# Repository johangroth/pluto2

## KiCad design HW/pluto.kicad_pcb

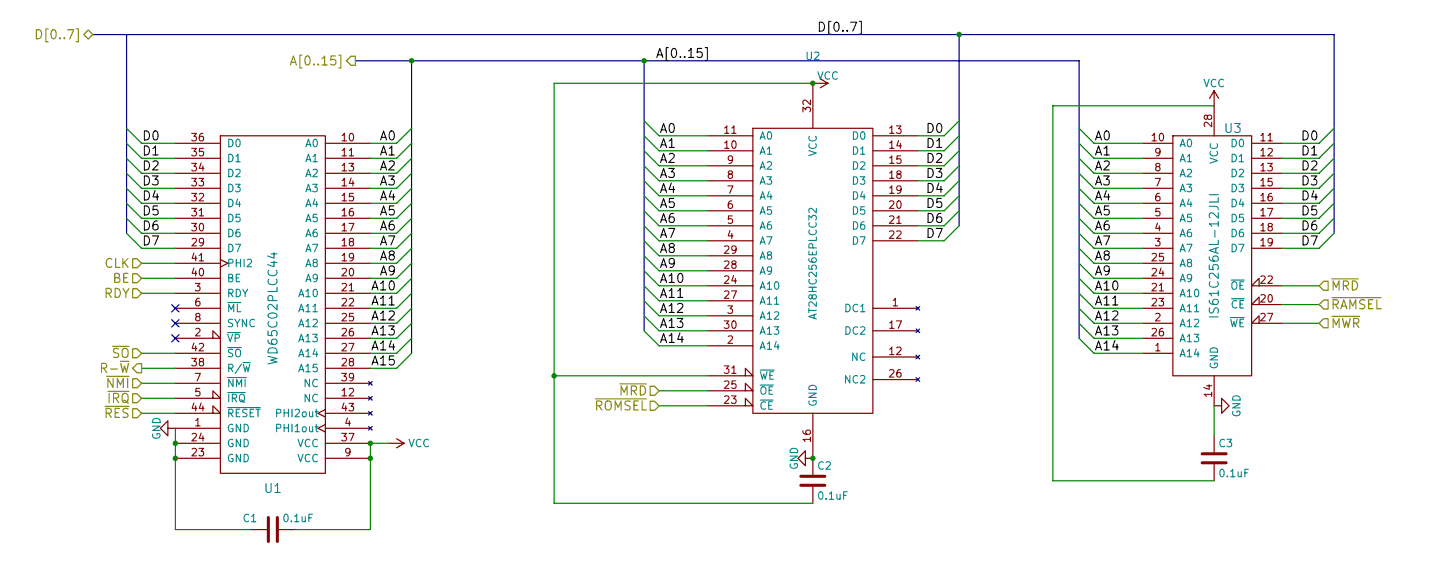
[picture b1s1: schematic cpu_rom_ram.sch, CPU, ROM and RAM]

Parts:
C1, C2, C3: 0.1uF; C_0805_2012Metric_Pad1.15x1.40mm_HandSolder
U1: WD65C02PLCC44; PLCC-44_THT-Socket
U2: AT28HC256EPLCC32; PLCC-32_THT-Socket
U3: IS61C256AL-12JLI; SOJ-28_7.585x18.12mm_P1.27mm

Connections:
/16bit IDE interface/A0: U1.10 (A0), U2.11 (A0), U3.10 (A0); also elsewhere on the board
/16bit IDE interface/A1: U1.11 (A1), U2.10 (A1), U3.9 (A1); also elsewhere on the board
/16bit IDE interface/A2: U1.13 (A2), U2.9 (A2), U3.8 (A2); also elsewhere on the board
/16bit IDE interface/A3: U1.14 (A3), U2.8 (A3), U3.7 (A3); also elsewhere on the board
/16bit IDE interface/CLK: U1.41 (PHI2); also elsewhere on the board
/16bit IDE interface/D0: U1.36 (D0), U2.13 (D0), U3.11 (D0); also elsewhere on the board
/16bit IDE interface/D1: U1.35 (D1), U2.14 (D1), U3.12 (D1); also elsewhere on the board
/16bit IDE interface/D2: U1.34 (D2), U2.15 (D2), U3.13 (D2); also elsewhere on the board
/16bit IDE interface/D3: U1.33 (D3), U2.18 (D3), U3.15 (D3); also elsewhere on the board
/16bit IDE interface/D4: U1.32 (D4), U2.19 (D4), U3.16 (D4); also elsewhere on the board
/16bit IDE interface/D5: U1.31 (D5), U2.20 (D5), U3.17 (D5); also elsewhere on the board
/16bit IDE interface/D6: U1.30 (D6), U2.21 (D6), U3.18 (D6); also elsewhere on the board
/16bit IDE interface/D7: U1.29 (D7), U2.22 (D7), U3.19 (D7); also elsewhere on the board
/16bit IDE interface/R-~W: U1.38 (R/~W); also elsewhere on the board
/16bit IDE interface/~IRQ: U1.5 (~IRQ); also elsewhere on the board
/16bit IDE interface/~RES: U1.44 (~RESET); also elsewhere on the board
/Address decoding and support section/A5: U1.16 (A5), U2.6 (A5), U3.5 (A5); also elsewhere on the board
/Address decoding and support section/A6: U1.17 (A6), U2.5 (A6), U3.4 (A6); also elsewhere on the board
/Address decoding and support section/A7: U1.18 (A7), U2.4 (A7), U3.3 (A7); also elsewhere on the board
/Address decoding and support section/A8: U1.19 (A8), U2.29 (A8), U3.25 (A8); also elsewhere on the board
/Address decoding and support section/A9: U1.20 (A9), U2.28 (A9), U3.24 (A9); also elsewhere on the board
/Address decoding and support section/A10: U1.21 (A10), U2.24 (A10), U3.21 (A10); also elsewhere on the board
/Address decoding and support section/A11: U1.22 (A11), U2.27 (A11), U3.23 (A11); also elsewhere on the board
/Address decoding and support section/A12: U1.25 (A12), U2.3 (A12), U3.2 (A12); also elsewhere on the board
/Address decoding and support section/A13: U1.26 (A13), U2.30 (A13), U3.26 (A13); also elsewhere on the board
/Address decoding and support section/A14: U1.27 (A14), U2.2 (A14), U3.1 (A14); also elsewhere on the board
/Address decoding and support section/A15: U1.28 (A15); also elsewhere on the board
/Address decoding and support section/BE: U1.40 (BE); also elsewhere on the board
/Address decoding and support section/RDY: U1.3 (RDY); also elsewhere on the board
/Address decoding and support section/~MRD: U2.25 (~OE), U3.22 (~OE); also elsewhere on the board
/Address decoding and support section/~MWR: U3.27 (~WE); also elsewhere on the board
/Address decoding and support section/~NMI: U1.7 (~NMI); also elsewhere on the board
/Address decoding and support section/~RAMSEL: U3.20 (~CE); also elsewhere on the board
/Address decoding and support section/~ROMSEL: U2.23 (~CE); also elsewhere on the board
/Address decoding and support section/~SO: U1.42 (~SO); also elsewhere on the board
/CPU, ROM and RAM/A4: U1.15 (A4), U2.7 (A4), U3.6 (A4); also elsewhere on the board
GND: C1.1, C2.1, C3.1, U1.1 (GND), U1.23 (GND), U1.24 (GND), U2.16 (GND), U3.14 (GND); also elsewhere on the board
VCC: C1.2, C2.2, C3.2, U1.9 (VCC), U1.37 (VCC), U2.31 (~WE), U2.32 (VCC), U3.28 (VCC); also elsewhere on the board

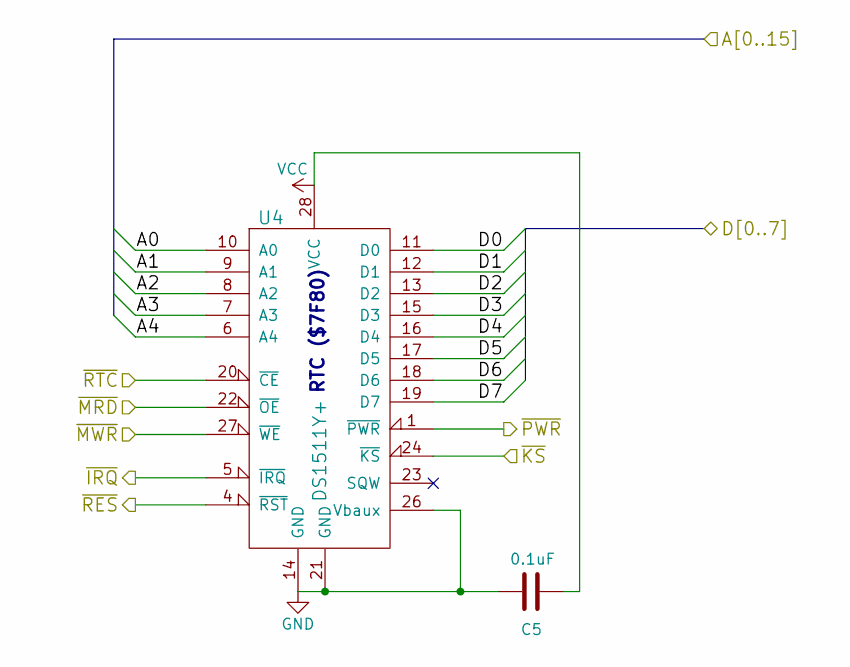
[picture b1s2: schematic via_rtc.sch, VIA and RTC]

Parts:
C5: 0.1uF; C_0805_2012Metric_Pad1.15x1.40mm_HandSolder
U4: DS1511Y+; DIP-28_W15.24mm_Socket

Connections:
/16bit IDE interface/A0: U4.10 (A0); also elsewhere on the board
/16bit IDE interface/A1: U4.9 (A1); also elsewhere on the board
/16bit IDE interface/A2: U4.8 (A2); also elsewhere on the board
/16bit IDE interface/A3: U4.7 (A3); also elsewhere on the board
/16bit IDE interface/D0: U4.11 (D0); also elsewhere on the board
/16bit IDE interface/D1: U4.12 (D1); also elsewhere on the board
/16bit IDE interface/D2: U4.13 (D2); also elsewhere on the board
/16bit IDE interface/D3: U4.15 (D3); also elsewhere on the board
/16bit IDE interface/D4: U4.16 (D4); also elsewhere on the board
/16bit IDE interface/D5: U4.17 (D5); also elsewhere on the board
/16bit IDE interface/D6: U4.18 (D6); also elsewhere on the board
/16bit IDE interface/D7: U4.19 (D7); also elsewhere on the board
/16bit IDE interface/~IRQ: U4.5 (~IRQ); also elsewhere on the board
/16bit IDE interface/~RES: U4.4 (~RST); also elsewhere on the board
/Address decoding and support section/~KS: U4.24 (~KS); also elsewhere on the board
/Address decoding and support section/~MRD: U4.22 (~OE); also elsewhere on the board
/Address decoding and support section/~MWR: U4.27 (~WE); also elsewhere on the board
/Address decoding and support section/~PWR: U4.1 (~PWR); also elsewhere on the board
/Address decoding and support section/~RTC: U4.20 (~CE); also elsewhere on the board
/CPU, ROM and RAM/A4: U4.6 (A4); also elsewhere on the board
GND: C5.2, U4.14 (GND), U4.21 (GND), U4.26 (Vbaux); also elsewhere on the board
VCC: C5.1, U4.28 (VCC); also elsewhere on the board

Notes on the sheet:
RTC ($7F80)

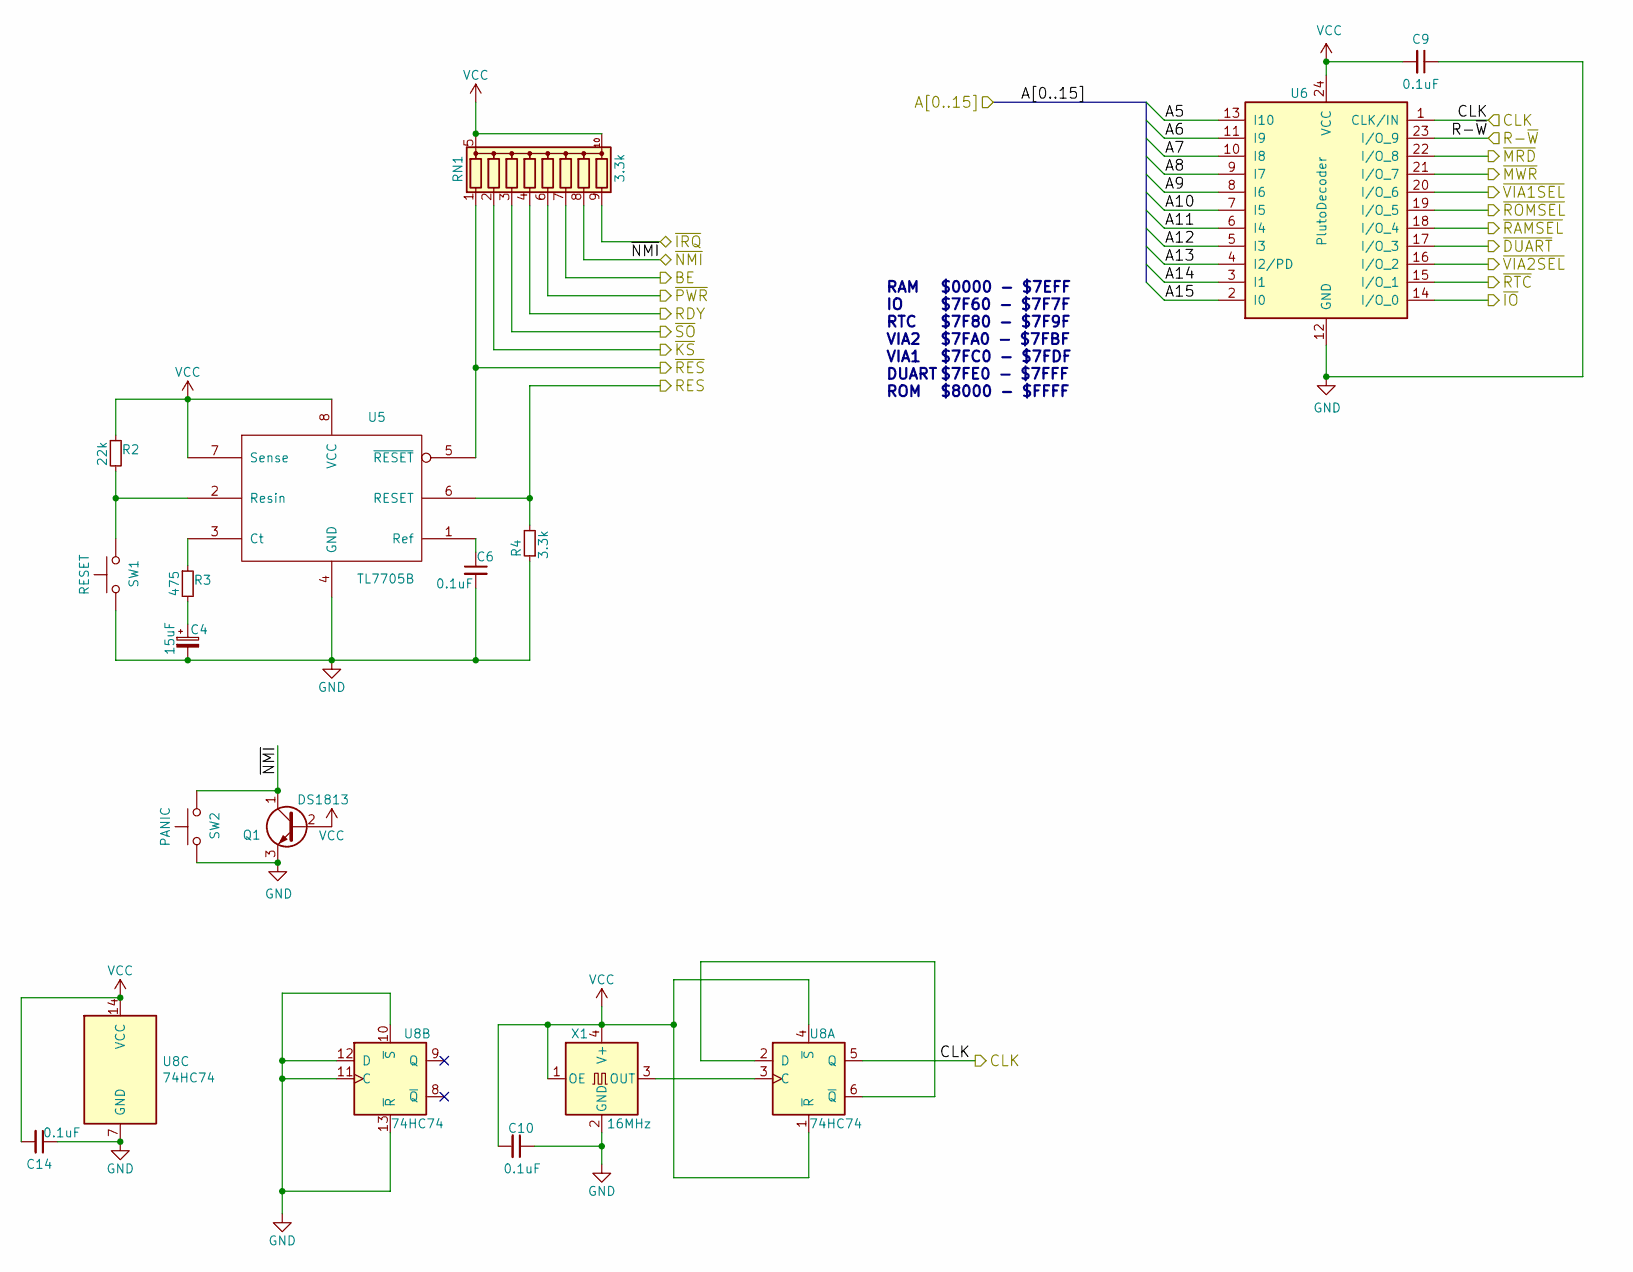
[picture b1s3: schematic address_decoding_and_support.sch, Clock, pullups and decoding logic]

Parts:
C4: 15uF; CP_EIA-3528-15_AVX-H_Pad1.50x2.35mm_HandSolder
C6, C9, C10, C14: 0.1uF; C_0805_2012Metric_Pad1.15x1.40mm_HandSolder
Q1: DS1813; SOT-23_Handsoldering
R2: 22k; R_1206_3216Metric_Pad1.42x1.75mm_HandSolder
R3: 475; R_1206_3216Metric_Pad1.42x1.75mm_HandSolder
R4: 3.3k; R_1206_3216Metric_Pad1.42x1.75mm_HandSolder
RN1: 3.3k; R_Array_Convex_5x1206
SW1: RESET; SW_PUSH_6mm_H4.3mm
SW2: PANIC; SW_PUSH_6mm_H4.3mm
U5: TL7705B; SOIC-8_3.9x4.9mm_P1.27mm
U6: PlutoDecoder; DIP-24_W7.62mm_Socket
U8: 74HC74; SOIC-14_3.9x8.7mm_P1.27mm
X1: 16MHz; Oscillator_SMD_SeikoEpson_SG8002CA-4Pin_7.0x5.0mm

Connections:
/16bit IDE interface/CLK: U6.1 (CLK/IN), U8.5 (Q); also elsewhere on the board
/16bit IDE interface/R-~W: U6.23 (I/O_9); also elsewhere on the board
/16bit IDE interface/~IRQ: RN1.9 (R8); also elsewhere on the board
/16bit IDE interface/~RES: RN1.1 (R1), U5.5 (~RESET); also elsewhere on the board
/16bit IDE interface/~VIA1SEL: U6.20 (I/O_6); also elsewhere on the board
/16bit IDE interface/~VIA2SEL: U6.16 (I/O_2); also elsewhere on the board
/Address decoding and support section/A5: U6.13 (I10); also elsewhere on the board
/Address decoding and support section/A6: U6.11 (I9); also elsewhere on the board
/Address decoding and support section/A7: U6.10 (I8); also elsewhere on the board
/Address decoding and support section/A8: U6.9 (I7); also elsewhere on the board
/Address decoding and support section/A9: U6.8 (I6); also elsewhere on the board
/Address decoding and support section/A10: U6.7 (I5); also elsewhere on the board
/Address decoding and support section/A11: U6.6 (I4); also elsewhere on the board
/Address decoding and support section/A12: U6.5 (I3); also elsewhere on the board
/Address decoding and support section/A13: U6.4 (I2/PD); also elsewhere on the board
/Address decoding and support section/A14: U6.3 (I1); also elsewhere on the board
/Address decoding and support section/A15: U6.2 (I0); also elsewhere on the board
/Address decoding and support section/BE: RN1.7 (R6); also elsewhere on the board
/Address decoding and support section/RDY: RN1.4 (R4); also elsewhere on the board
/Address decoding and support section/RES: R4.2, U5.6 (RESET); also elsewhere on the board
/Address decoding and support section/~DUART: U6.17 (I/O_3); also elsewhere on the board
/Address decoding and support section/~IO: U6.14 (I/O_0); also elsewhere on the board
/Address decoding and support section/~KS: RN1.2 (R2); also elsewhere on the board
/Address decoding and support section/~MRD: U6.22 (I/O_8); also elsewhere on the board
/Address decoding and support section/~MWR: U6.21 (I/O_7); also elsewhere on the board
/Address decoding and support section/~NMI: Q1.1 (C), RN1.8 (R7), SW2.2; also elsewhere on the board
/Address decoding and support section/~PWR: RN1.6 (R5); also elsewhere on the board
/Address decoding and support section/~RAMSEL: U6.18 (I/O_4); also elsewhere on the board
/Address decoding and support section/~ROMSEL: U6.19 (I/O_5); also elsewhere on the board
/Address decoding and support section/~RTC: U6.15 (I/O_1); also elsewhere on the board
/Address decoding and support section/~SO: RN1.3 (R3); also elsewhere on the board
GND: C4.2, C6.2, C9.1, C10.1, C14.1, Q1.3 (E), R4.1, SW1.1, SW2.1, U5.4 (GND), U6.12 (GND), U8.7 (GND), U8.10 (~S), U8.11 (C), U8.12 (D), U8.13 (~R), X1.2 (GND); also elsewhere on the board
unnamed: C4.1, R3.2
unnamed: C6.1, U5.1 (Ref)
unnamed: R2.2, SW1.2, U5.2 (Resin)
unnamed: R3.1, U5.3 (Ct)
unnamed: U8.2 (D), U8.6 (~Q)
unnamed: U8.3 (C), X1.3 (OUT)
VCC: C9.2, C10.2, C14.2, Q1.2 (B), R2.1, RN1.5 (common), RN1.10 (common), U5.7 (Sense), U5.8 (VCC), U6.24 (VCC), U8.1 (~R), U8.4 (~S), U8.14 (VCC), X1.1 (OE), X1.4 (V+); also elsewhere on the board

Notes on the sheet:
RAM IO RTC VIA2 VIA1 DUART ROM
$0000 - $7EFF $7F60 - $7F7F $7F80 - $7F9F $7FA0 - $7FBF $7FC0 - $7FDF $7FE0 - $7FFF $8000 - $FFFF

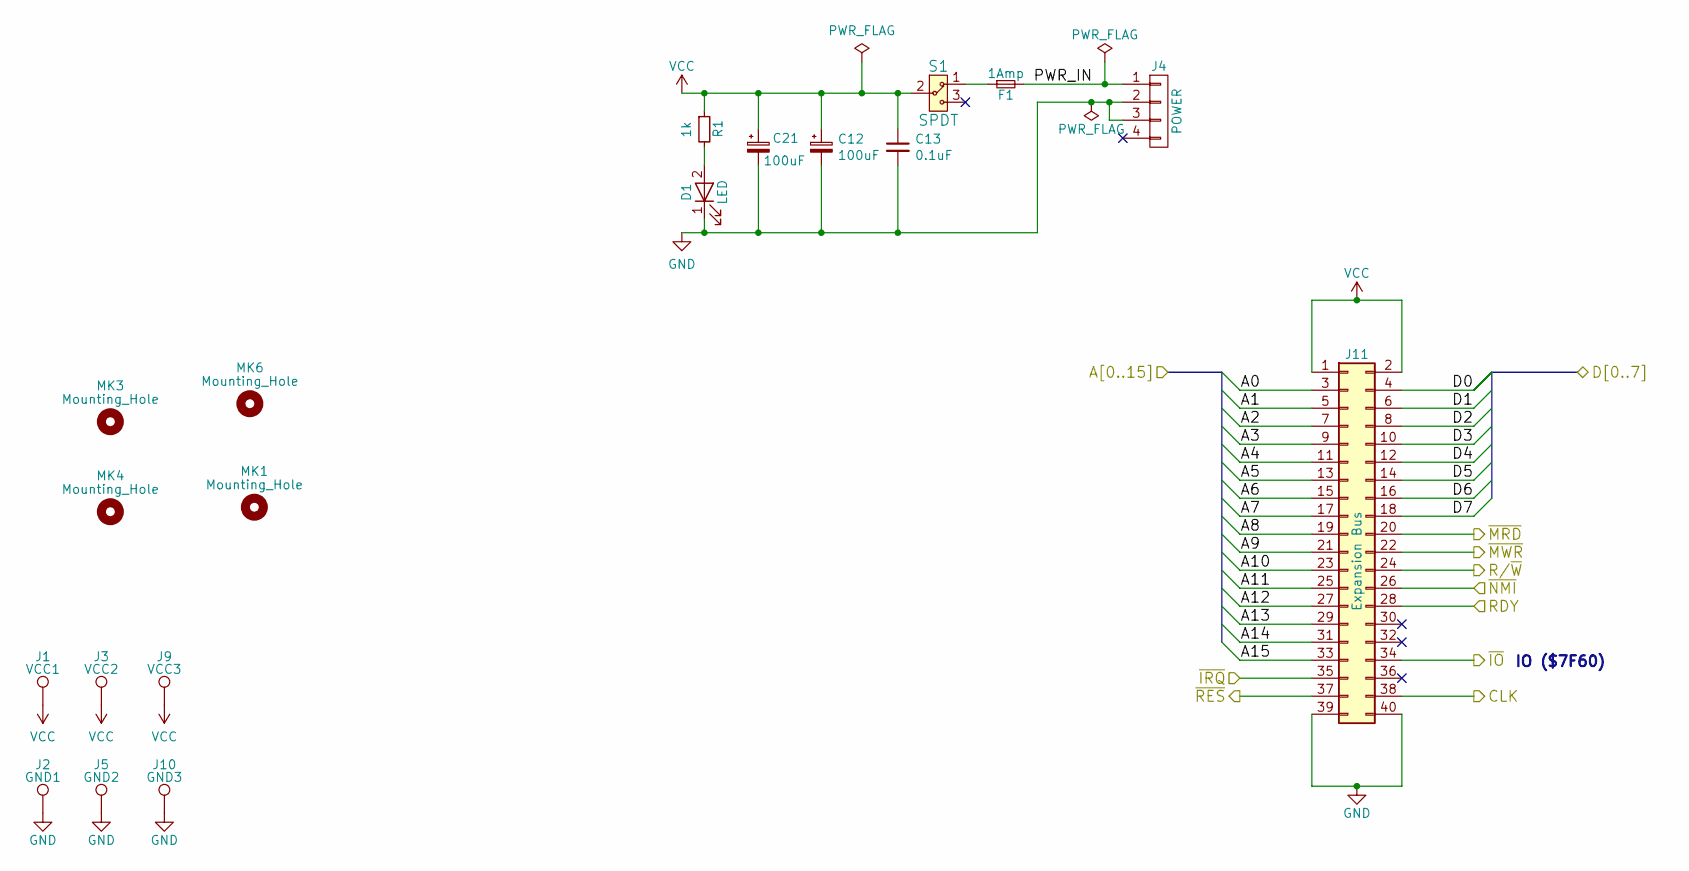
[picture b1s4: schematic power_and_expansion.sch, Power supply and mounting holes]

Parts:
C12, C21: 100uF; CP_EIA-3528-15_AVX-H_Pad1.50x2.35mm_HandSolder
C13: 0.1uF; C_0805_2012Metric_Pad1.15x1.40mm_HandSolder
D1: LED; LED_D3.0mm
F1: 1Amp; FUSE_0154004.DR
J1: VCC1; PinHeader_1x01_P2.54mm_Vertical
J2: GND1; PinHeader_1x01_P2.54mm_Vertical
J3: VCC2; PinHeader_1x01_P2.54mm_Vertical
J4: POWER; Molex_Nano-Fit_105313-xx04_1x04_P2.50mm_Horizontal
J5: GND2; PinHeader_1x01_P2.54mm_Vertical
J9: VCC3; PinHeader_1x01_P2.54mm_Vertical
J10: GND3; PinHeader_1x01_P2.54mm_Vertical
J11: Expansion Bus; IDC-Header_2x20_P2.54mm_Vertical
MK1, MK3, MK4, MK6: Mounting_Hole; MountingHole_3.2mm_M3_Pad
R1: 1k; R_1206_3216Metric_Pad1.42x1.75mm_HandSolder
S1: SPDT; SW-SPDT-0900766b81587629

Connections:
/16bit IDE interface/A0: J11.3; also elsewhere on the board
/16bit IDE interface/A1: J11.5; also elsewhere on the board
/16bit IDE interface/A2: J11.7; also elsewhere on the board
/16bit IDE interface/A3: J11.9; also elsewhere on the board
/16bit IDE interface/CLK: J11.38; also elsewhere on the board
/16bit IDE interface/D0: J11.4; also elsewhere on the board
/16bit IDE interface/D1: J11.6; also elsewhere on the board
/16bit IDE interface/D2: J11.8; also elsewhere on the board
/16bit IDE interface/D3: J11.10; also elsewhere on the board
/16bit IDE interface/D4: J11.12; also elsewhere on the board
/16bit IDE interface/D5: J11.14; also elsewhere on the board
/16bit IDE interface/D6: J11.16; also elsewhere on the board
/16bit IDE interface/D7: J11.18; also elsewhere on the board
/16bit IDE interface/R-~W: J11.24; also elsewhere on the board
/16bit IDE interface/~IRQ: J11.35; also elsewhere on the board
/16bit IDE interface/~RES: J11.37; also elsewhere on the board
/Address decoding and support section/A5: J11.13; also elsewhere on the board
/Address decoding and support section/A6: J11.15; also elsewhere on the board
/Address decoding and support section/A7: J11.17; also elsewhere on the board
/Address decoding and support section/A8: J11.19; also elsewhere on the board
/Address decoding and support section/A9: J11.21; also elsewhere on the board
/Address decoding and support section/A10: J11.23; also elsewhere on the board
/Address decoding and support section/A11: J11.25; also elsewhere on the board
/Address decoding and support section/A12: J11.27; also elsewhere on the board
/Address decoding and support section/A13: J11.29; also elsewhere on the board
/Address decoding and support section/A14: J11.31; also elsewhere on the board
/Address decoding and support section/A15: J11.33; also elsewhere on the board
/Address decoding and support section/RDY: J11.28; also elsewhere on the board
/Address decoding and support section/~IO: J11.34; also elsewhere on the board
/Address decoding and support section/~MRD: J11.20; also elsewhere on the board
/Address decoding and support section/~MWR: J11.22; also elsewhere on the board
/Address decoding and support section/~NMI: J11.26; also elsewhere on the board
/CPU, ROM and RAM/A4: J11.11; also elsewhere on the board
/Power and mounting holes/PWR_IN: F1.2, J4.1
GND: C12.2, C13.2, C21.2, D1.1 (K), J2.1, J4.2, J4.3, J5.1, J10.1, J11.39, J11.40; also elsewhere on the board
unnamed: D1.2 (A), R1.2
unnamed: F1.1, S1.1
VCC: C12.1, C13.1, C21.1, J1.1, J3.1, J9.1, J11.1, J11.2, R1.1, S1.2 (COM); also elsewhere on the board

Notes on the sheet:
IO ($7F60)

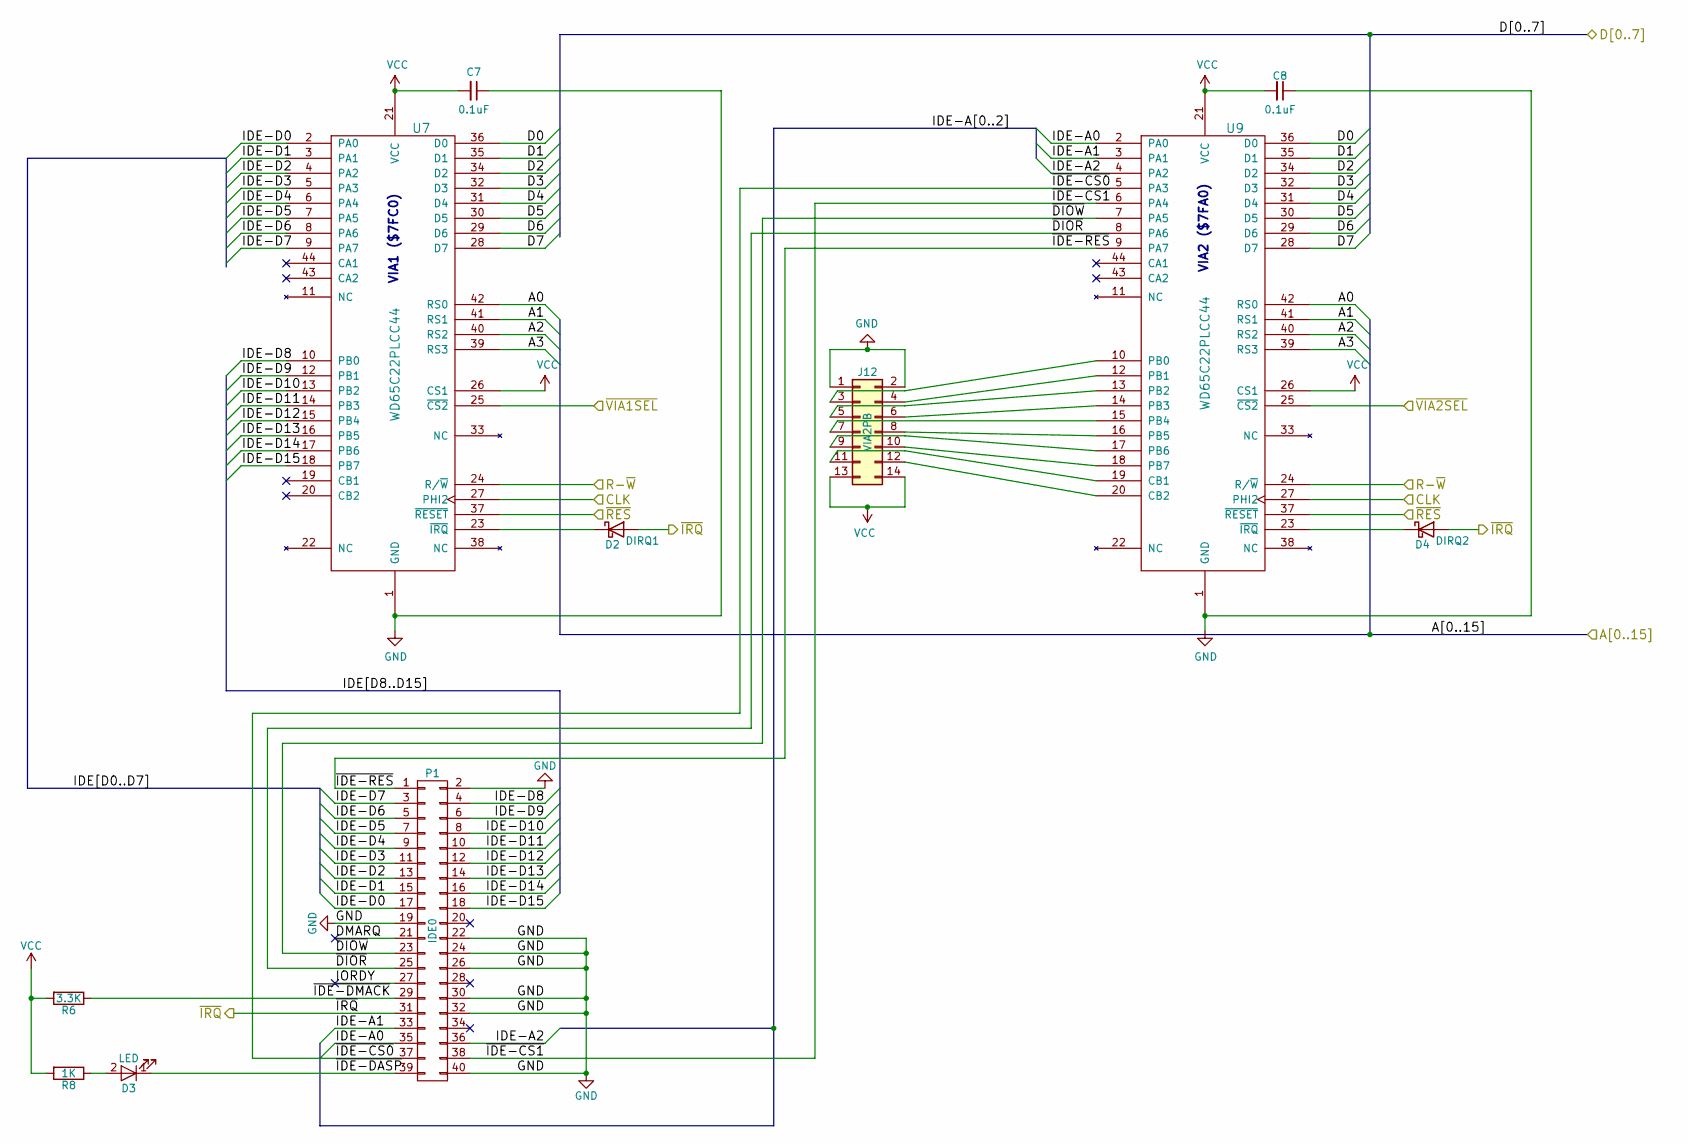
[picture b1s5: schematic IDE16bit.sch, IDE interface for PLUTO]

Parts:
C7, C8: 0.1uF; C_0805_2012Metric_Pad1.15x1.40mm_HandSolder
D2: DIRQ1; D_SOD-323_HandSoldering
D3: LED; LED_D3.0mm
D4: DIRQ2; D_SOD-323_HandSoldering
J12: VIA2PB; IDC-Header_2x07_P2.54mm_Vertical
P1: IDE0; IDC-Header_2x20_P2.54mm_Vertical
R6: 3.3K; R_1206_3216Metric_Pad1.42x1.75mm_HandSolder
R8: 1K; R_1206_3216Metric_Pad1.42x1.75mm_HandSolder
U7, U9: WD65C22PLCC44; PLCC-44_THT-Socket

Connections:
/16bit IDE interface/A0: U7.42 (RS0), U9.42 (RS0); also elsewhere on the board
/16bit IDE interface/A1: U7.41 (RS1), U9.41 (RS1); also elsewhere on the board
/16bit IDE interface/A2: U7.40 (RS2), U9.40 (RS2); also elsewhere on the board
/16bit IDE interface/A3: U7.39 (RS3), U9.39 (RS3); also elsewhere on the board
/16bit IDE interface/CLK: U7.27 (PHI2), U9.27 (PHI2); also elsewhere on the board
/16bit IDE interface/D0: U7.36 (D0), U9.36 (D0); also elsewhere on the board
/16bit IDE interface/D1: U7.35 (D1), U9.35 (D1); also elsewhere on the board
/16bit IDE interface/D2: U7.34 (D2), U9.34 (D2); also elsewhere on the board
/16bit IDE interface/D3: U7.32 (D3), U9.32 (D3); also elsewhere on the board
/16bit IDE interface/D4: U7.31 (D4), U9.31 (D4); also elsewhere on the board
/16bit IDE interface/D5: U7.30 (D5), U9.30 (D5); also elsewhere on the board
/16bit IDE interface/D6: U7.29 (D6), U9.29 (D6); also elsewhere on the board
/16bit IDE interface/D7: U7.28 (D7), U9.28 (D7); also elsewhere on the board
/16bit IDE interface/DMARQ: P1.21
/16bit IDE interface/IDE-A0: P1.35, U9.2 (PA0)
/16bit IDE interface/IDE-A1: P1.33, U9.3 (PA1)
/16bit IDE interface/IDE-A2: P1.36, U9.4 (PA2)
/16bit IDE interface/IDE-D0: P1.17, U7.2 (PA0)
/16bit IDE interface/IDE-D1: P1.15, U7.3 (PA1)
/16bit IDE interface/IDE-D2: P1.13, U7.4 (PA2)
/16bit IDE interface/IDE-D3: P1.11, U7.5 (PA3)
/16bit IDE interface/IDE-D4: P1.9, U7.6 (PA4)
/16bit IDE interface/IDE-D5: P1.7, U7.7 (PA5)
/16bit IDE interface/IDE-D6: P1.5, U7.8 (PA6)
/16bit IDE interface/IDE-D7: P1.3, U7.9 (PA7)
/16bit IDE interface/IDE-D8: P1.4, U7.10 (PB0)
/16bit IDE interface/IDE-D9: P1.6, U7.12 (PB1)
/16bit IDE interface/IDE-D10: P1.8, U7.13 (PB2)
/16bit IDE interface/IDE-D11: P1.10, U7.14 (PB3)
/16bit IDE interface/IDE-D12: P1.12, U7.15 (PB4)
/16bit IDE interface/IDE-D13: P1.14, U7.16 (PB5)
/16bit IDE interface/IDE-D14: P1.16, U7.17 (PB6)
/16bit IDE interface/IDE-D15: P1.18, U7.18 (PB7)
/16bit IDE interface/IORDY: P1.27
/16bit IDE interface/R-~W: U7.24 (R/~W), U9.24 (R/~W); also elsewhere on the board
/16bit IDE interface/~DIOR: P1.25, U9.8 (PA6)
/16bit IDE interface/~DIOW: P1.23, U9.7 (PA5)
/16bit IDE interface/~IDE-CS0: P1.37, U9.5 (PA3)
/16bit IDE interface/~IDE-CS1: P1.38, U9.6 (PA4)
/16bit IDE interface/~IDE-DASP: D3.1 (K), P1.39
/16bit IDE interface/~IDE-DMACK: P1.29, R6.1
/16bit IDE interface/~IDE-RES: P1.1, U9.9 (PA7)
/16bit IDE interface/~IRQ: D2.2 (A), D4.2 (A), P1.31; also elsewhere on the board
/16bit IDE interface/~RES: U7.37 (~RESET), U9.37 (~RESET); also elsewhere on the board
/16bit IDE interface/~VIA1SEL: U7.25 (~CS2); also elsewhere on the board
/16bit IDE interface/~VIA2SEL: U9.25 (~CS2); also elsewhere on the board
GND: C7.1, C8.1, J12.1, J12.2, P1.2, P1.19, P1.22, P1.24, P1.26, P1.30, P1.32, P1.40, U7.1 (GND), U9.1 (GND); also elsewhere on the board
unnamed: D2.1 (K), U7.23 (~IRQ)
unnamed: D3.2 (A), R8.1
unnamed: D4.1 (K), U9.23 (~IRQ)
unnamed: J12.3, U9.10 (PB0)
unnamed: J12.4, U9.12 (PB1)
unnamed: J12.5, U9.13 (PB2)
unnamed: J12.6, U9.14 (PB3)
unnamed: J12.7, U9.15 (PB4)
unnamed: J12.8, U9.16 (PB5)
unnamed: J12.9, U9.17 (PB6)
unnamed: J12.10, U9.18 (PB7)
unnamed: J12.11, U9.19 (CB1)
unnamed: J12.12, U9.20 (CB2)
VCC: C7.2, C8.2, J12.13, J12.14, R6.2, R8.2, U7.21 (VCC), U7.26 (CS1), U9.21 (VCC), U9.26 (CS1); also elsewhere on the board

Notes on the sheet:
VIA1 ($7FC0)
VIA2 ($7FA0)

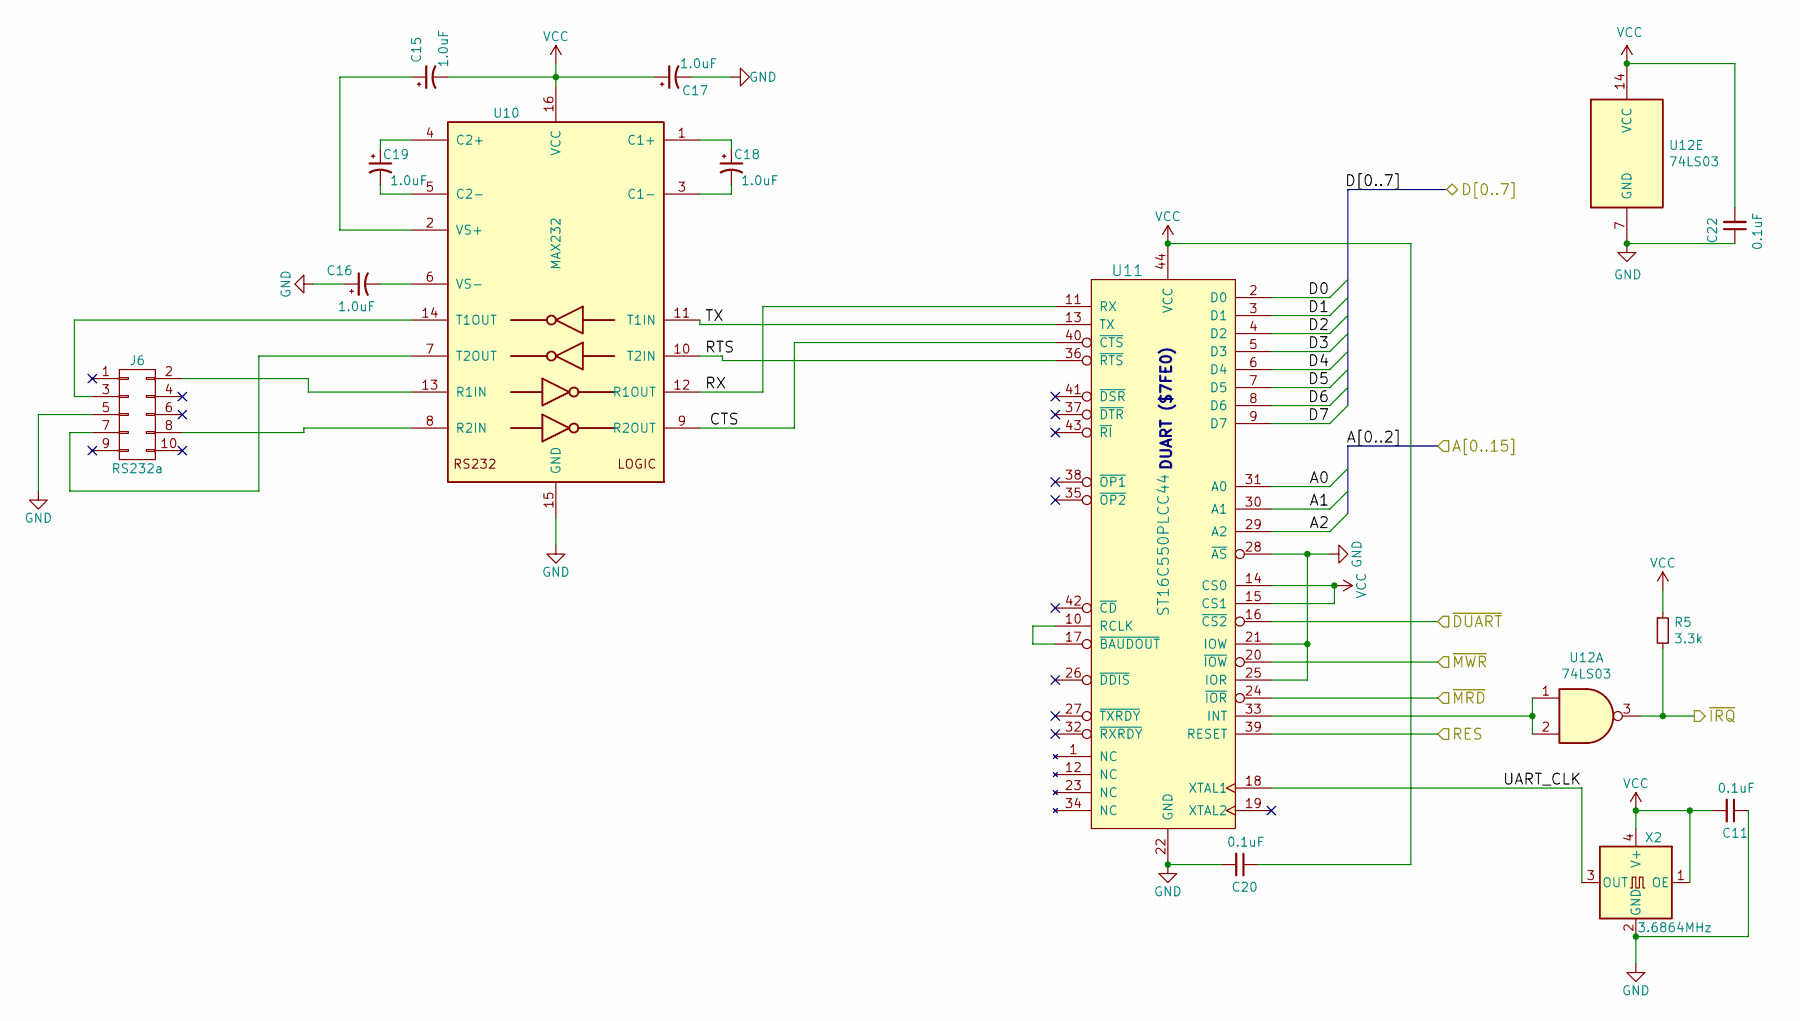
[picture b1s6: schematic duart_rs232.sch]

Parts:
C11, C20, C22: 0.1uF; C_0805_2012Metric_Pad1.15x1.40mm_HandSolder
C15, C16, C17, C18, C19: 1.0uF; CP_EIA-3528-21_Kemet-B_Pad1.50x2.35mm_HandSolder
J6: RS232a; IDC-Header_2x05_P2.54mm_Vertical
R5: 3.3k; R_1206_3216Metric_Pad1.42x1.75mm_HandSolder
U10: MAX232; SOIC-16W_7.5x10.3mm_P1.27mm
U11: ST16C550PLCC44; PLCC-44_THT-Socket
U12: 74LS03; SOIC-14_3.9x8.7mm_P1.27mm
X2: 3.6864MHz; Oscillator_SMD_SeikoEpson_SG8002CA-4Pin_7.0x5.0mm

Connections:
/16bit IDE interface/A0: U11.31 (A0); also elsewhere on the board
/16bit IDE interface/A1: U11.30 (A1); also elsewhere on the board
/16bit IDE interface/A2: U11.29 (A2); also elsewhere on the board
/16bit IDE interface/D0: U11.2 (D0); also elsewhere on the board
/16bit IDE interface/D1: U11.3 (D1); also elsewhere on the board
/16bit IDE interface/D2: U11.4 (D2); also elsewhere on the board
/16bit IDE interface/D3: U11.5 (D3); also elsewhere on the board
/16bit IDE interface/D4: U11.6 (D4); also elsewhere on the board
/16bit IDE interface/D5: U11.7 (D5); also elsewhere on the board
/16bit IDE interface/D6: U11.8 (D6); also elsewhere on the board
/16bit IDE interface/D7: U11.9 (D7); also elsewhere on the board
/16bit IDE interface/~IRQ: R5.2, U12.3; also elsewhere on the board
/Address decoding and support section/RES: U11.39 (RESET); also elsewhere on the board
/Address decoding and support section/~DUART: U11.16 (~CS2); also elsewhere on the board
/Address decoding and support section/~MRD: U11.24 (~IOR); also elsewhere on the board
/Address decoding and support section/~MWR: U11.20 (~IOW); also elsewhere on the board
/DUART and RS232/CTS: U10.9 (R2OUT), U11.40 (~CTS)
/DUART and RS232/RTS: U10.10 (T2IN), U11.36 (~RTS)
/DUART and RS232/RX: U10.12 (R1OUT), U11.11 (RX)
/DUART and RS232/TX: U10.11 (T1IN), U11.13 (TX)
/DUART and RS232/UART_CLK: U11.18 (XTAL1), X2.3 (OUT)
GND: C11.1, C16.1, C17.2, C20.2, C22.1, J6.5, U10.15 (GND), U11.21 (IOW), U11.22 (GND), U11.25 (IOR), U11.28 (~AS), U12.7 (GND), X2.2 (GND); also elsewhere on the board
unnamed: C15.1, U10.2 (VS+)
unnamed: C16.2, U10.6 (VS-)
unnamed: C18.1, U10.1 (C1+)
unnamed: C18.2, U10.3 (C1-)
unnamed: C19.1, U10.4 (C2+)
unnamed: C19.2, U10.5 (C2-)
unnamed: J6.2, U10.13 (R1IN)
unnamed: J6.3, U10.14 (T1OUT)
unnamed: J6.7, U10.7 (T2OUT)
unnamed: J6.8, U10.8 (R2IN)
unnamed: U11.10 (RCLK), U11.17 (~BAUDOUT)
unnamed: U11.33 (INT), U12.1, U12.2
VCC: C11.2, C15.2, C17.1, C20.1, C22.2, R5.1, U10.16 (VCC), U11.14 (CS0), U11.15 (CS1), U11.44 (VCC), U12.14 (VCC), X2.1 (OE), X2.4 (V+); also elsewhere on the board

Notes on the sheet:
DUART ($7FE0)

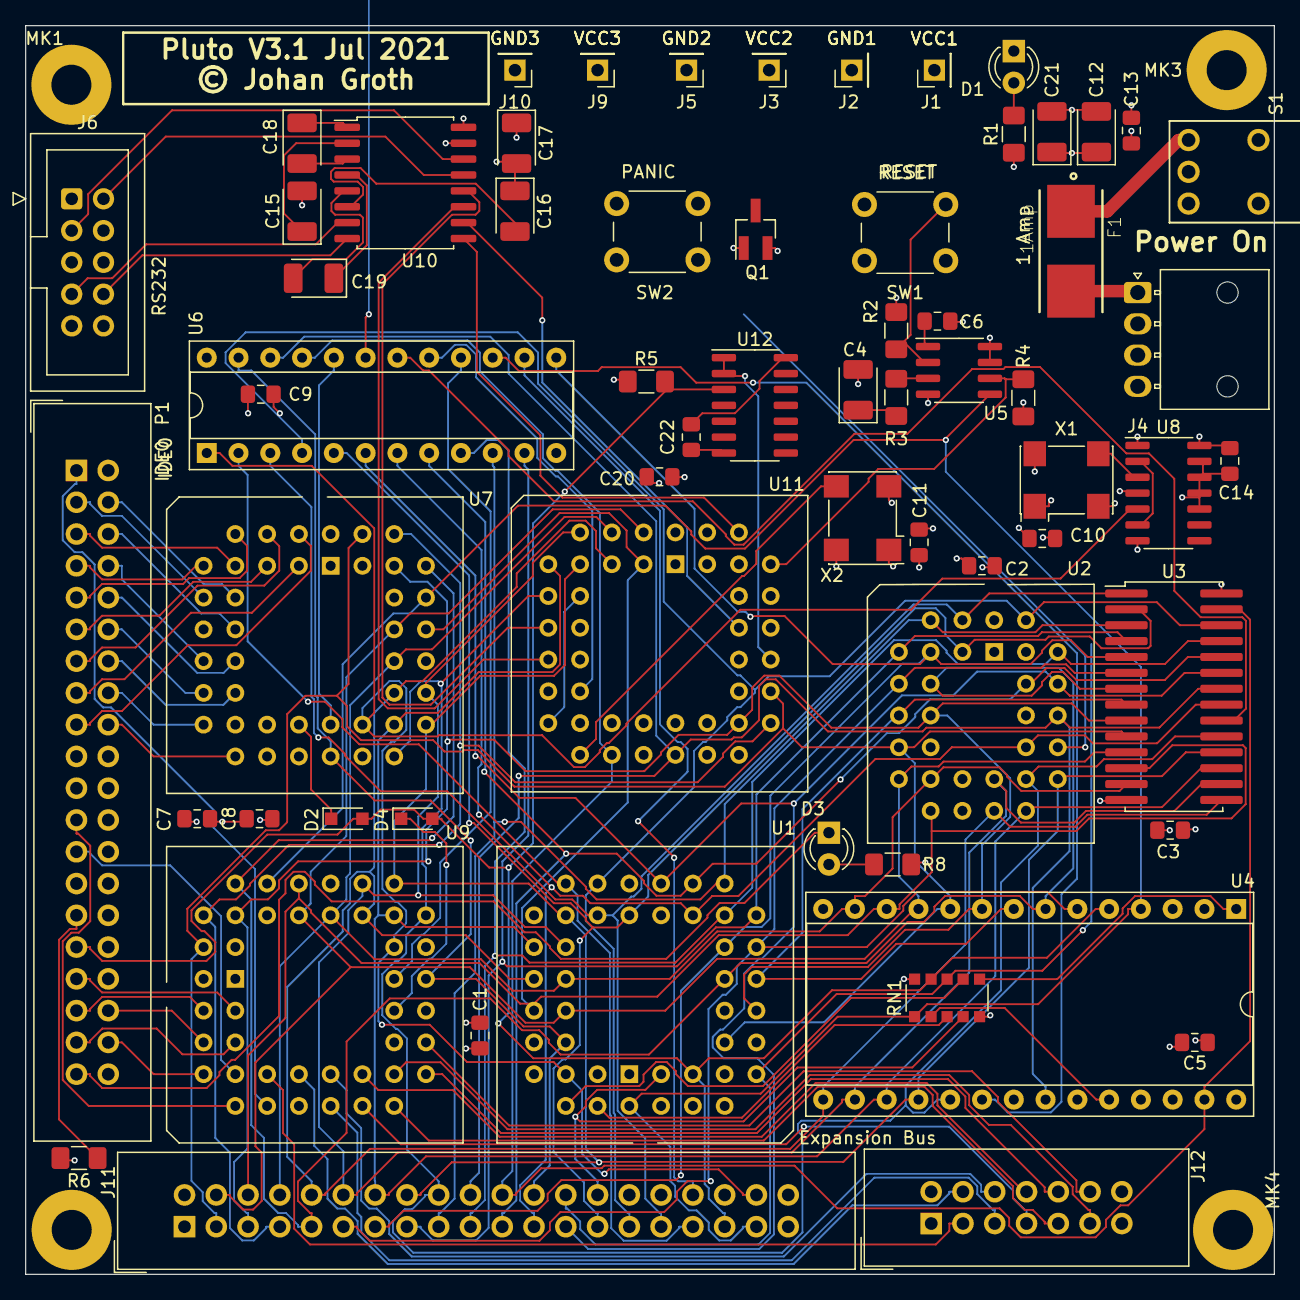
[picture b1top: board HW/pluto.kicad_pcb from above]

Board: 4 copper layers, 99.8 x 99.8 mm, 68 parts (0 on the bottom side), 111 nets.

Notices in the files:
HW/pluto.kicad_pcb:
© Johan Groth
